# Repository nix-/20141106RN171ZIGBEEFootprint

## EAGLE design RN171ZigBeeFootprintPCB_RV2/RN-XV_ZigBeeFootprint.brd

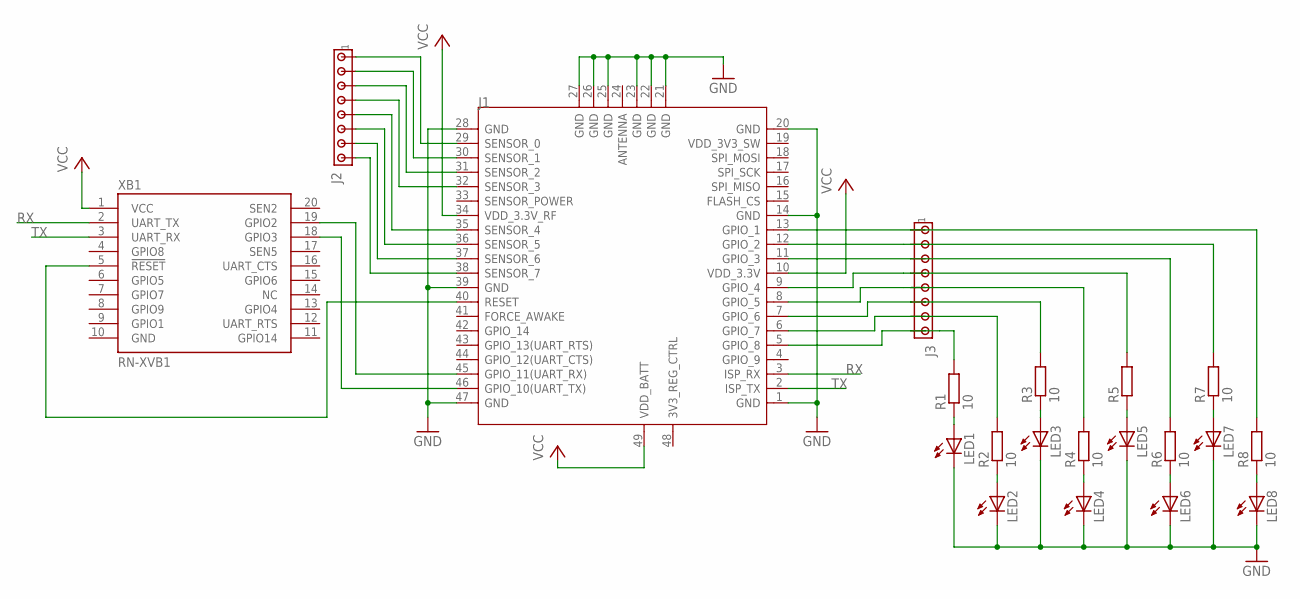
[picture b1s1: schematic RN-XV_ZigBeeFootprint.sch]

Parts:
J1: MODULE_WIFI-RN-171; MODULE_49P-1.27-26.67X17.78
J2, J3: MTA08-100; 10X08MTA
LED1, LED2, LED3, LED4, LED5, LED6, LED7, LED8: LED_ELD260; LED_LD260
R1, R2, R3, R4, R6, R7, R8: 10; MINI_MELF-0102W
R5: R-EU_MELF0102W; MINI_MELF-0102W
XB1: RN-XVB1; XBEE

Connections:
GND: J1.1 (GND), J1.14 (GND), J1.20 (GND), J1.21 (GND), J1.22 (GND), J1.23 (GND), J1.25 (GND), J1.26 (GND), J1.27 (GND), J1.28 (GND), J1.39 (GND), J1.47 (GND), LED1.K (C), LED2.K (C), LED3.K (C), LED4.K (C), LED5.K (C), LED6.K (C), LED7.K (C), LED8.K (C), XB1.10 (GND)
unnamed: J1.38 (SENSOR_7), J2.8
unnamed: J1.37 (SENSOR_6), J2.7
unnamed: J1.40 (RESET), XB1.5 (!RESET)
unnamed: J1.46 (GPIO_10(UART_TX)), XB1.18 (GPIO3)
unnamed: J1.45 (GPIO_11(UART_RX)), XB1.19 (GPIO2)
unnamed: J1.36 (SENSOR_5), J2.6
unnamed: J1.35 (SENSOR_4), J2.5
unnamed: J1.32 (SENSOR_3), J2.4
unnamed: J1.30 (SENSOR_1), J2.2
unnamed: J1.29 (SENSOR_0), J2.1
unnamed: J1.31 (SENSOR_2), J2.3
unnamed: LED1.A, R1.1
unnamed: LED2.A, R2.1
unnamed: LED3.A, R3.1
unnamed: LED4.A, R4.1
unnamed: LED5.A, R5.1
unnamed: LED6.A, R6.1
unnamed: LED7.A, R7.1
unnamed: LED8.A, R8.1
unnamed: J1.5 (GPIO_8), J3.8, R1.2
unnamed: J1.6 (GPIO_7), J3.7, R2.2
unnamed: J1.7 (GPIO_6), J3.6, R3.2
unnamed: J1.8 (GPIO_5), J3.5, R4.2
unnamed: J1.9 (GPIO_4), J3.4, R5.2
unnamed: J1.11 (GPIO_3), J3.3, R6.2
unnamed: J1.12 (GPIO_2), J3.2, R7.2
unnamed: J1.13 (GPIO_1), J3.1, R8.2
RX: J1.3 (ISP_RX), XB1.2 (UART_TX)
TX: J1.2 (ISP_TX), XB1.3 (UART_RX)
VDD_3.3V: J1.10 (VDD_3.3V), J1.34 (VDD_3.3V_RF), J1.49 (VDD_BATT), XB1.1 (VCC)

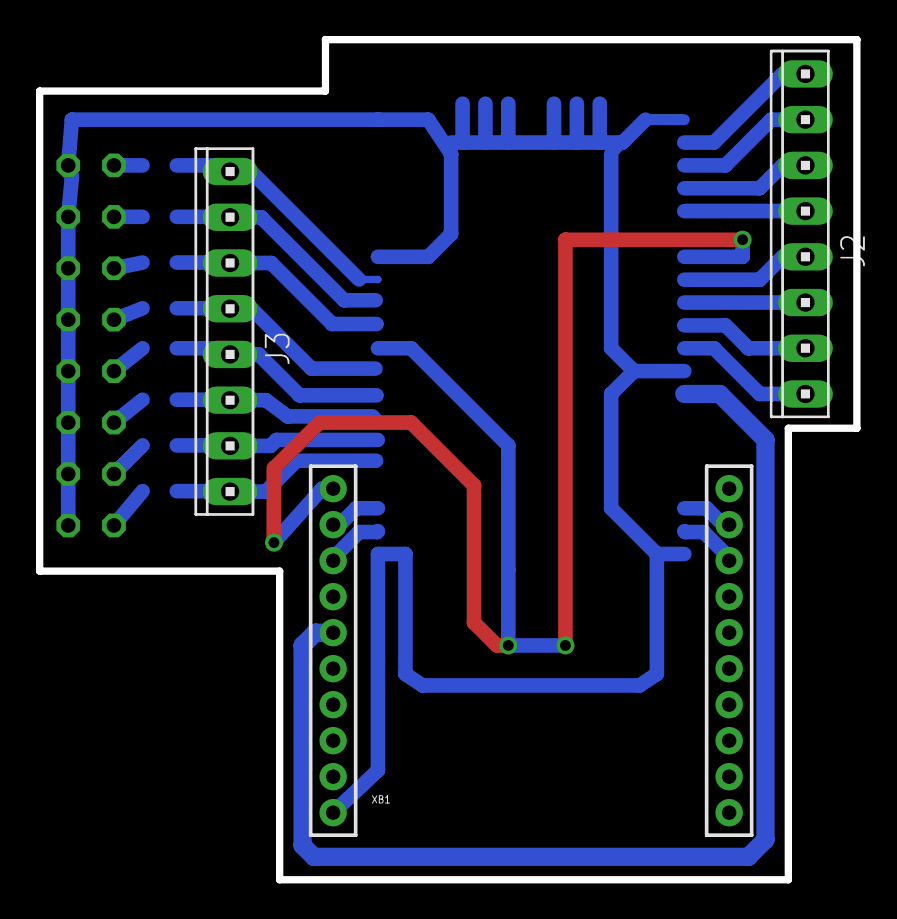
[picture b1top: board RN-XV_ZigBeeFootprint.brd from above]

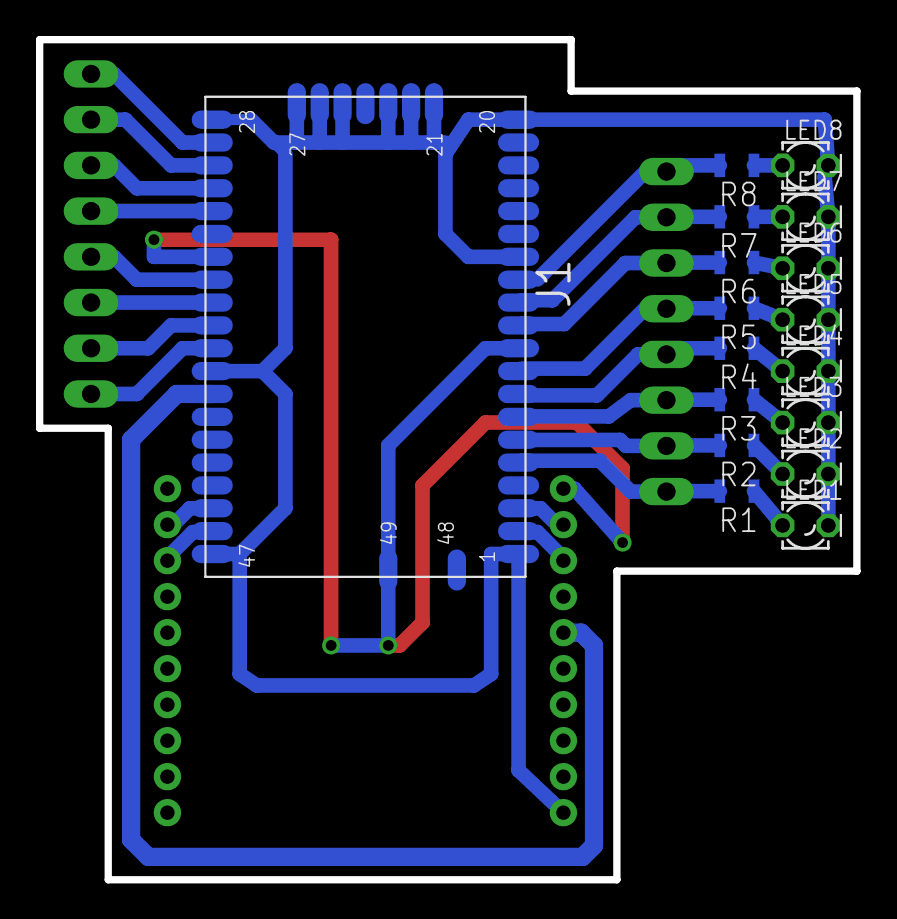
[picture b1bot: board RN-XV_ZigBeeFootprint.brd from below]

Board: 2 copper layers, 45.4 x 46.7 mm, 20 parts (17 on the bottom side), 31 nets.

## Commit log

2014-11-06 Added Foot libraries and PCB for REV1
2014-11-06 Connecting GND to the circuit
2014-11-06 added Exchange Certificate File
2014-11-06 Added Revision 2. Added LED in to design.
2014-11-06 Wired LED in to the PCB design.
2014-11-06 Connecting voltage supply to all components.
2014-11-06 Connecting RN171's 34 pin to VCC
2014-11-06 Replace one of the line in the PCB design.
2016-01-04 test commite ssh
